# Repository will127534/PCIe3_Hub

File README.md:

# RPI5 PCIe 3.0 Hub
An opensource PCIe 3.0 Hub design based on ASM2806 with Raspberry Pi 5's PCIe FPC connector design

## Important note

ASM2806A != ASM2806, this design is using ASM2806 specifically.

## Introduction

So basically this is the follow-up on [this](https://www.willwhang.dev/Solar-eclipse-2024/#pcie-30-hub-development), that I finally found a schematic containing how to use [ASM2806](https://www.asmedia.com.tw/product/012Yq70sX2zI9xN5/7c5YQ79xz8urEGr1), which is a PCIe 3.0 hub with x2 upstream and four x1 downstream.  

The board is designed to give that schematic a try, so it is not really designed like those PCIe 2.0 NVMe hub RPi hat designs you might have seen before. Its design is to make my life easier when debugging/soldering it. (i.e single sided components + 5cm x 5cm board size).

Also, because I'm going to build a few boards for RPi5 that I want to have a PCIe 3.0 hub with, all the PCIe connectors on board are the same as RPi’s PCIe FPC "[standard](https://datasheets.raspberrypi.com/pcie/pcie-connector-standard.pdf)", and the testing is also done on RPi5.

Is it working? Yeap!

## Detailed notes

So if you compare the PCB files here and the one in the photo, you can see that there is a jump wire in the photo. At the same time, if you look at the PCB files, there are two jumper JP1 and JP2. This is because RPI5 FPC has a power enable signal, where the device should use this signal to power down and up. However, this makes the debugging (checking rail voltage) process slightly difficult, so the jumper here is for forcing ASM2806/downstream device power on. JP1 is for ASM2806 power enable signal, either connect it directly to 5V or using the RPI enable signal. JP2 is the downstream PCIe FPC power enable signal, and it is either 3.3V or RPI enable signal. The one shown in the photo has the downstream PCIe FPC power enable signal bodge wired to the RPI enable signal, and that has been fixed in the PCB file here on GitHub.

For ASM2806, it is configured as four downstream ports with each getting x1 PCIe 3.0. Both upstream clock and downstream clock are based on 100Mhz PCIe clock. No SPI flash is required to function (thankfully). It requires three voltages: 3.3V/2.5V/1.05V. Most of the DC-DC converter here is just grabbing the design/parts I have on my hand and are overspec a bit so you can change it for sure. For the rail naming, there is also 3.3V suspend, but I connected it to 3.3V directly, and the 1.05V I'm following the schematic to add some filtering.

Surprisingly, it doesn't take that much power. As you can see in the power consumption table in the schematic, I can stress test without a heatsink for hours, but the chip does get hot to touch. If that worries you, then you might have to consider adding a small heatsink, especially if the PCB copper is not large enough to dissipate the heat.

There are some signals that I'm interested in, specifically the HOTPLUG signal, and it is attached to a test pad, but I'm not able to see it function by pulling this pin up or down.

Finally, the thing that caught me during the test is how the schematic connects the crystal. In the schematic, there is a 10pf cap on the XO/XI pins, which I'm still quite puzzled about (Normally, I expect to see like a 1M ohm resistor across for the Crystal driver), but it is necessary to have this chip work.

## Performance

Yes, each PCIe downstream device independently can consume up to PCIe 3.0 x1 speed, but once you have more than one going, I’m surprised the bandwidth doesn't seem to be equally shared. I'm not quite sure if that is caused by the tool I use to stress test (four NVMe drives + FIO), or is it caused by the NVMe drive itself (maximum supported MPS). Following Jeff Geerling's [guide](https://www.jeffgeerling.com/blog/2021/getting-faster-10-gbps-ethernet-on-raspberry-pi) I've also enabled pci=pcie_bus_perf and the hub can support up to 512 byte MPS also:

```
[    0.752521] pci 0000:00:00.0: Max Payload Size set to  512/ 512 (was  128), Max Read Rq  512
[    0.752532] pci 0000:01:00.0: Max Payload Size set to  512/ 512 (was  128), Max Read Rq  512
[    0.752543] pci 0000:02:00.0: Max Payload Size set to  512/ 512 (was  128), Max Read Rq  512
[    0.752558] pci 0000:03:00.0: Max Payload Size set to  512/ 512 (was  128), Max Read Rq  512
[    0.752568] pci 0000:02:02.0: Max Payload Size set to  512/ 512 (was  128), Max Read Rq  512
[    0.752588] pci 0000:04:00.0: Max Payload Size set to  128/ 128 (was  128), Max Read Rq  128
[    0.752598] pci 0000:02:06.0: Max Payload Size set to  512/ 512 (was  128), Max Read Rq  512
[    0.752616] pci 0000:05:00.0: Max Payload Size set to  256/ 256 (was  128), Max Read Rq  256
[    0.752627] pci 0000:02:0e.0: Max Payload Size set to  512/ 512 (was  128), Max Read Rq  512
[    0.752644] pci 0000:06:00.0: Max Payload Size set to  256/ 256 (was  128), Max Read Rq  256
```

## Footnotes
* [Interactive BOM](https://htmlpreview.github.io/?https://github.com/will127534/PCIe3_Hub/blob/main/bom/ibom.html) [(provided by InteractiveHtmlBom)
](https://github.com/openscopeproject/InteractiveHtmlBom)
* designed with Kicad v8.0
* Please refrain from inquiring about the source of the chip. Additionally, please note that this chip is quite expensive (approximately 15-20 USD), which is one of the reasons why you may not have encountered any PCIe 3.0 hubs for RPi5 other than this one.

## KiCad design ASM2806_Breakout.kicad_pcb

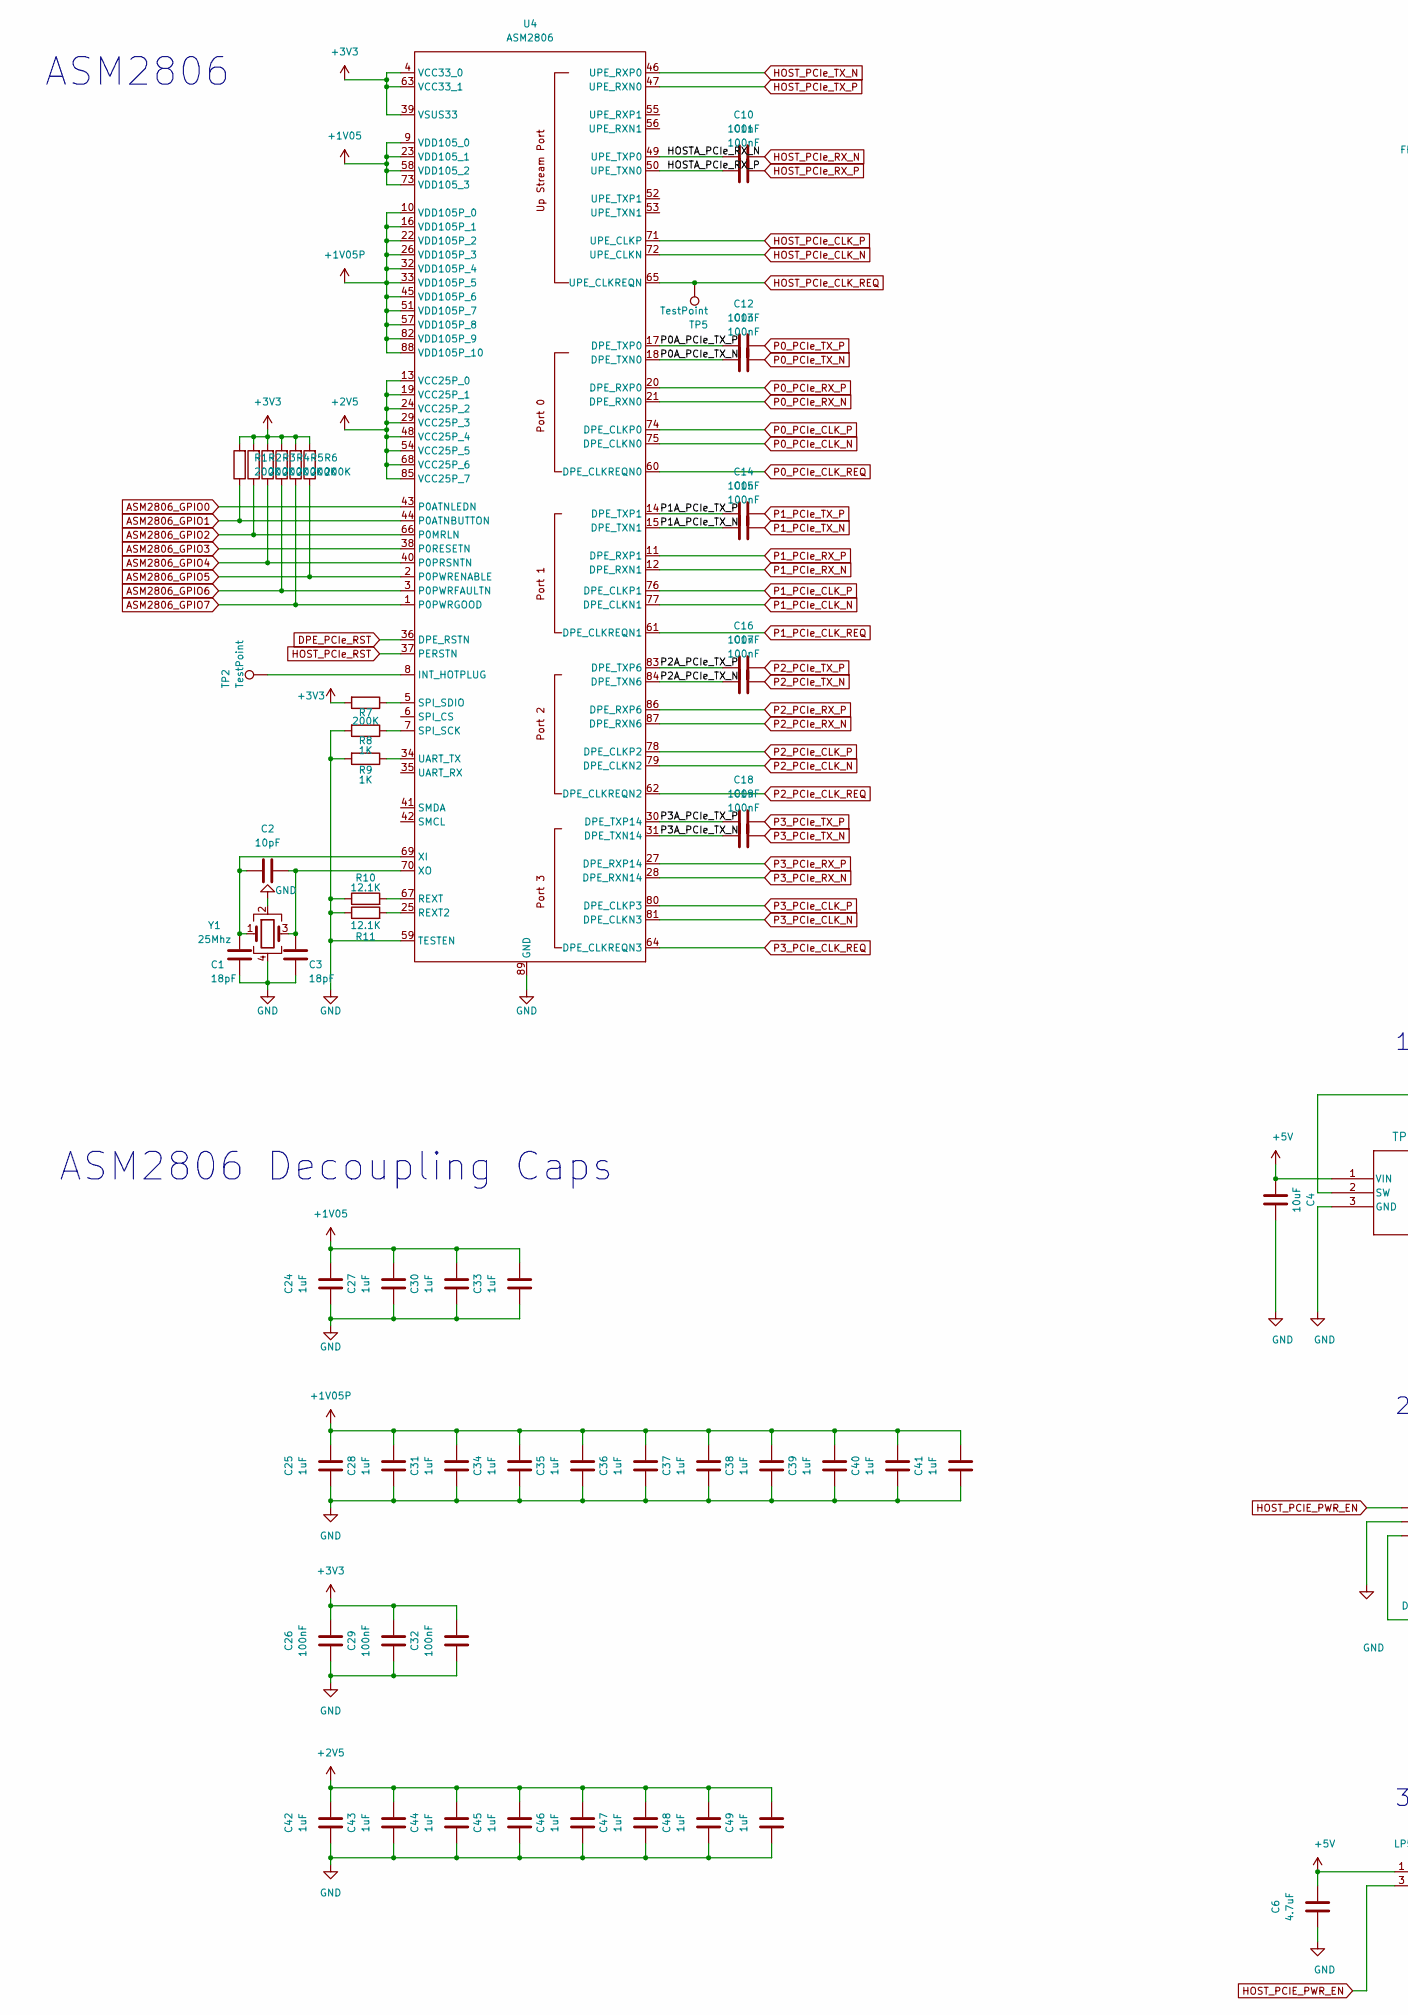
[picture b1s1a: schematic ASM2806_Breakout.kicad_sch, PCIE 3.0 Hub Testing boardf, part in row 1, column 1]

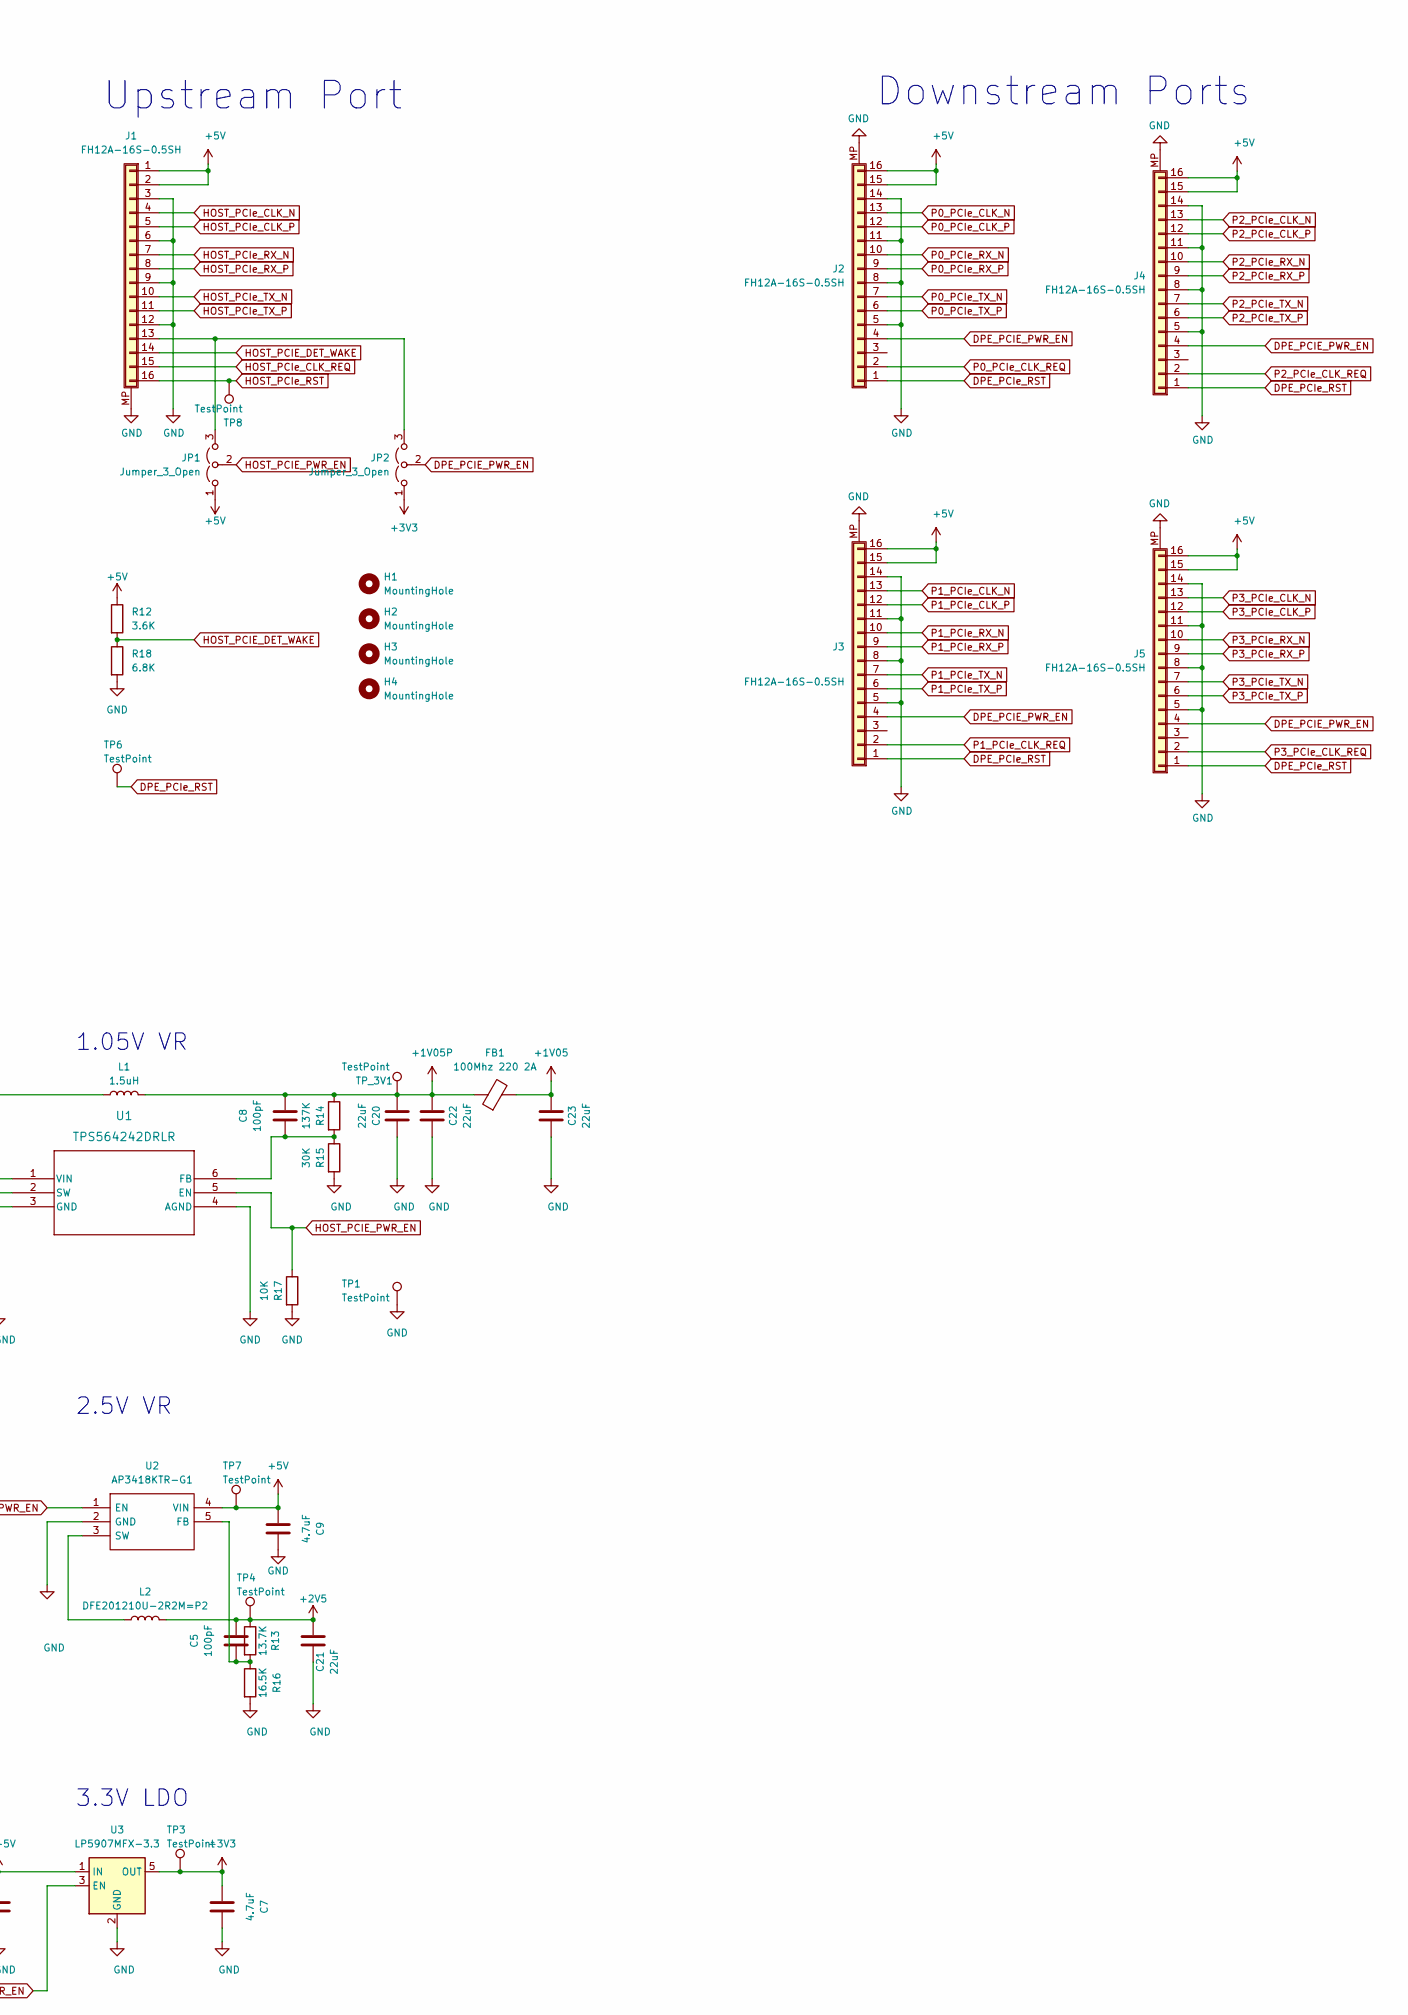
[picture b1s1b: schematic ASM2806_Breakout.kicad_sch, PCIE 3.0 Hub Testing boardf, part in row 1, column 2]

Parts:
C1, C3: 18pF; C_0402_1005Metric
C2: 10pF; C_0402_1005Metric
C4: 10uF; C_0805_2012Metric
C5, C8: 100pF; C_0402_1005Metric
C6, C7, C9: 4.7uF; C_0603_1608Metric
C10, C11, C12, C13, C14, C15, C16, C17, C18, C19, C26, C29, C32: 100nF; C_0402_1005Metric
C20, C22, C23: 22uF; C_0805_2012Metric
C21: 22uF; C_0603_1608Metric
C24, C25, C27, C28, C30, C31, C33, C34, C35, C36, C37, C38, C39, C40, C41, C42, C43, C44, C45, C46, C47, C48, C49: 1uF; C_0402_1005Metric
FB1: 100Mhz 220 2A; L_0603_1608Metric
H1, H2, H3, H4: MountingHole; MountingHole_2.5mm
J1, J2, J3, J4, J5: FH12A-16S-0.5SH; Hirose_FH12-16S-0.5SH_1x16-1MP_P0.50mm_Horizontal
JP1, JP2: Jumper_3_Open; SolderJumper-3_P1.3mm_Open_RoundedPad1.0x1.5mm_NumberLabels
L1: 1.5uH; L_Vishay_IHLP-1616
L2: DFE201210U-2R2M=P2; L_0805_2012Metric
R1, R2, R3, R4, R5, R6, R7: 200K; R_0402_1005Metric
R8, R9: 1K; R_0402_1005Metric
R10, R11: 12.1K; R_0402_1005Metric
R12: 3.6K; R_0402_1005Metric
R13: 13.7K; R_0402_1005Metric
R14: 137K; R_0402_1005Metric
R15: 30K; R_0402_1005Metric
R16: 16.5K; R_0402_1005Metric
R17: 10K; R_0402_1005Metric
R18: 6.8K; R_0402_1005Metric
TP1, TP2, TP3, TP4, TP5, TP6, TP7, TP8: TestPoint; TestPoint_Pad_D1.0mm
TP_3V1: TestPoint; TestPoint_Pad_D1.0mm
U1: TPS564242DRLR; TPS564242DRLR_TEX
U2: AP3418KTR-G1; SOT-23-5; Mouser Part Number 621-AP3418KTR-G1
U3: LP5907MFX-3.3; SOT-23-5
U4: ASM2806; QFN-88_EP_10x10_Pitch0.4mm
Y1: 25Mhz; Crystal_SMD_Abracon_ABM8G-4Pin_3.2x2.5mm

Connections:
+1V05: C23.2, C24.2, C27.2, C30.2, C33.2, FB1.2, U4.9 (VDD105_0), U4.23 (VDD105_1), U4.58 (VDD105_2), U4.73 (VDD105_3)
+1V05P: C8.2, C20.1, C22.2, C25.2, C28.2, C31.2, C34.2, C35.2, C36.2, C37.2, C38.2, C39.2, C40.2, C41.2, FB1.1, L1.2, R14.1, TP_3V1.1, U4.10 (VDD105P_0), U4.16 (VDD105P_1), U4.22 (VDD105P_2), U4.26 (VDD105P_3), U4.32 (VDD105P_4), U4.33 (VDD105P_5), U4.45 (VDD105P_6), U4.51 (VDD105P_7), U4.57 (VDD105P_8), U4.82 (VDD105P_9), U4.88 (VDD105P_10)
+2V5: C5.2, C21.2, C42.2, C43.2, C44.2, C45.2, C46.2, C47.2, C48.2, C49.2, L2.2, R13.1, TP4.1, U4.13 (VCC25P_0), U4.19 (VCC25P_1), U4.24 (VCC25P_2), U4.29 (VCC25P_3), U4.48 (VCC25P_4), U4.54 (VCC25P_5), U4.68 (VCC25P_6), U4.85 (VCC25P_7)
+3V3: C7.1, C26.2, C29.2, C32.2, JP2.1 (A), R1.2, R2.2, R3.2, R4.2, R5.2, R6.2, R7.2, TP3.1, U3.5 (OUT), U4.4 (VCC33_0), U4.39 (VSUS33), U4.63 (VCC33_1)
+5V: C4.1, C6.2, C9.1, J1.1, J1.2, J2.15, J2.16, J3.15, J3.16, J4.15, J4.16, J5.15, J5.16, JP1.1 (A), R12.1, TP7.1, U1.1 (VIN), U2.4 (VIN), U3.1 (IN)
/HOSTA_PCIe_RX_N: C10.1, U4.49 (UPE_TXP0)
/HOSTA_PCIe_RX_P: C11.1, U4.50 (UPE_TXN0)
/P0A_PCIe_TX_N: C13.1, U4.18 (DPE_TXN0)
/P0A_PCIe_TX_P: C12.1, U4.17 (DPE_TXP0)
/P1A_PCIe_TX_N: C15.1, U4.15 (DPE_TXN1)
/P1A_PCIe_TX_P: C14.1, U4.14 (DPE_TXP1)
/P2A_PCIe_TX_N: C17.1, U4.84 (DPE_TXN6)
/P2A_PCIe_TX_P: C16.1, U4.83 (DPE_TXP6)
/P3A_PCIe_TX_N: C19.1, U4.31 (DPE_TXN14)
/P3A_PCIe_TX_P: C18.1, U4.30 (DPE_TXP14)
ASM2806_GPIO0: U4.43 (P0ATNLEDN)
ASM2806_GPIO1: R1.1, U4.44 (P0ATNBUTTON)
ASM2806_GPIO2: R2.1, U4.66 (P0MRLN)
ASM2806_GPIO3: U4.38 (P0RESETN)
ASM2806_GPIO4: R3.1, U4.40 (P0PRSNTN)
ASM2806_GPIO5: R6.1, U4.2 (P0PWRENABLE)
ASM2806_GPIO6: R4.1, U4.3 (P0PWRFAULTN)
ASM2806_GPIO7: R5.1, U4.1 (P0PWRGOOD)
DPE_PCIE_PWR_EN: J2.4, J3.4, J4.4, J5.4, JP2.2 (C)
DPE_PCIe_RST: J2.1, J3.1, J4.1, J5.1, TP6.1, U4.36 (DPE_RSTN)
GND: C1.2, C3.2, C4.2, C6.1, C7.2, C9.2, C20.2, C21.1, C22.1, C23.1, C24.1, C25.1, C26.1, C27.1, C28.1, C29.1, C30.1, C31.1, C32.1, C33.1, C34.1, C35.1, C36.1, C37.1, C38.1, C39.1, C40.1, C41.1, C42.1, C43.1, C44.1, C45.1, C46.1, C47.1, C48.1, C49.1, J1.3, J1.6, J1.9, J1.12, J1.MP (Shield), J2.5, J2.8, J2.11, J2.14, J2.MP (Shield), J3.5, J3.8, J3.11, J3.14, J3.MP (Shield), J4.5, J4.8, J4.11, J4.14, J4.MP (Shield), J5.5, J5.8, J5.11, J5.14, J5.MP (Shield), R8.2, R9.2, R10.1, R11.1, R15.2, R16.2, R17.2, R18.2, TP1.1, U1.3 (GND), U1.4 (AGND), U2.2 (GND), U3.2 (GND), U4.59 (TESTEN), U4.89 (GND), Y1.2, Y1.4
HOST_PCIE_DET_WAKE: J1.14, R12.2, R18.1
HOST_PCIE_PWR_EN: JP1.2 (C), R17.1, U1.5 (EN), U2.1 (EN), U3.3 (EN)
HOST_PCIe_CLK_N: J1.4, U4.72 (UPE_CLKN)
HOST_PCIe_CLK_P: J1.5, U4.71 (UPE_CLKP)
HOST_PCIe_CLK_REQ: J1.15, TP5.1, U4.65 (UPE_CLKREQN)
HOST_PCIe_RST: J1.16, TP8.1, U4.37 (PERSTN)
HOST_PCIe_RX_N: C10.2, J1.7
HOST_PCIe_RX_P: C11.2, J1.8
HOST_PCIe_TX_N: J1.10, U4.46 (UPE_RXP0)
HOST_PCIe_TX_P: J1.11, U4.47 (UPE_RXN0)
unnamed: J1.13, JP1.3 (B), JP2.3 (B)
unnamed: C8.1, R14.2, R15.1, U1.6 (FB)
unnamed: L1.1, U1.2 (SW)
unnamed: C5.1, R13.2, R16.1, U2.5 (FB)
unnamed: L2.1, U2.3 (SW)
unnamed: TP2.1, U4.8 (INT_HOTPLUG)
unnamed: R11.2, U4.25 (REXT2)
unnamed: R10.2, U4.67 (REXT)
unnamed: R8.1, U4.7 (SPI_SCK)
unnamed: R7.1, U4.5 (SPI_SDIO)
unnamed: R9.1, U4.34 (UART_TX)
unnamed: C1.1, C2.1, U4.69 (XI), Y1.1
unnamed: C2.2, C3.1, U4.70 (XO), Y1.3
P0_PCIe_CLK_N: J2.13, U4.75 (DPE_CLKN0)
P0_PCIe_CLK_P: J2.12, U4.74 (DPE_CLKP0)
P0_PCIe_CLK_REQ: J2.2, U4.60 (DPE_CLKREQN0)
P0_PCIe_RX_N: J2.10, U4.21 (DPE_RXN0)
P0_PCIe_RX_P: J2.9, U4.20 (DPE_RXP0)
P0_PCIe_TX_N: C13.2, J2.7
P0_PCIe_TX_P: C12.2, J2.6
P1_PCIe_CLK_N: J3.13, U4.77 (DPE_CLKN1)
P1_PCIe_CLK_P: J3.12, U4.76 (DPE_CLKP1)
P1_PCIe_CLK_REQ: J3.2, U4.61 (DPE_CLKREQN1)
P1_PCIe_RX_N: J3.10, U4.12 (DPE_RXN1)
P1_PCIe_RX_P: J3.9, U4.11 (DPE_RXP1)
P1_PCIe_TX_N: C15.2, J3.7
P1_PCIe_TX_P: C14.2, J3.6
P2_PCIe_CLK_N: J4.13, U4.79 (DPE_CLKN2)
P2_PCIe_CLK_P: J4.12, U4.78 (DPE_CLKP2)
P2_PCIe_CLK_REQ: J4.2, U4.62 (DPE_CLKREQN2)
P2_PCIe_RX_N: J4.10, U4.87 (DPE_RXN6)
P2_PCIe_RX_P: J4.9, U4.86 (DPE_RXP6)
P2_PCIe_TX_N: C17.2, J4.7
P2_PCIe_TX_P: C16.2, J4.6
P3_PCIe_CLK_N: J5.13, U4.81 (DPE_CLKN3)
P3_PCIe_CLK_P: J5.12, U4.80 (DPE_CLKP3)
P3_PCIe_CLK_REQ: J5.2, U4.64 (DPE_CLKREQN3)
P3_PCIe_RX_N: J5.10, U4.28 (DPE_RXN14)
P3_PCIe_RX_P: J5.9, U4.27 (DPE_RXP14)
P3_PCIe_TX_N: C19.2, J5.7
P3_PCIe_TX_P: C18.2, J5.6

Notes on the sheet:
2.5V VR
ASM2806
3.3V LDO
Upstream Port
1.05V VR
ASM2806 Decoupling Caps
Downstream Ports

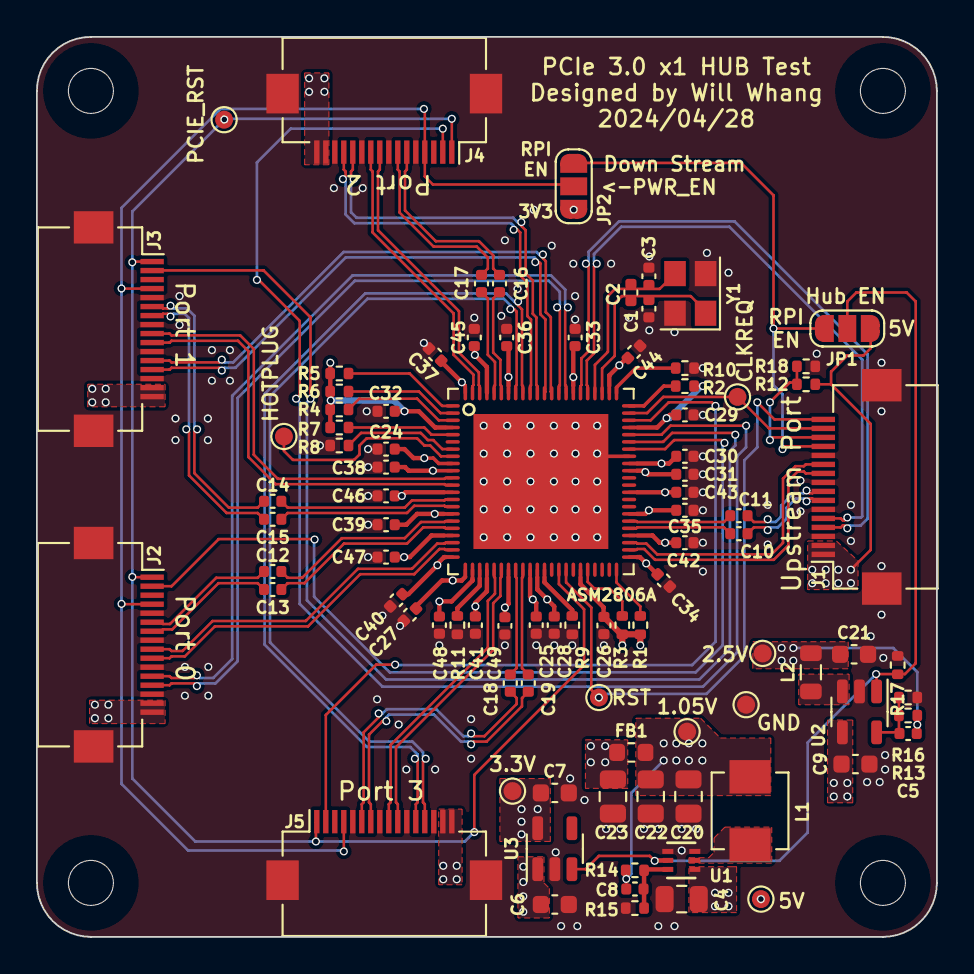
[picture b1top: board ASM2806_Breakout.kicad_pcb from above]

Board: 4 copper layers, 50.0 x 50.0 mm, 95 parts (0 on the bottom side), 75 nets.

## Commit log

2024-11-09 Init
